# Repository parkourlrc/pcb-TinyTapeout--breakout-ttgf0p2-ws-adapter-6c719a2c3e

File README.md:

# Tiny Tapeout GF 0p2 mezzanine adapter PCB

&emsp;

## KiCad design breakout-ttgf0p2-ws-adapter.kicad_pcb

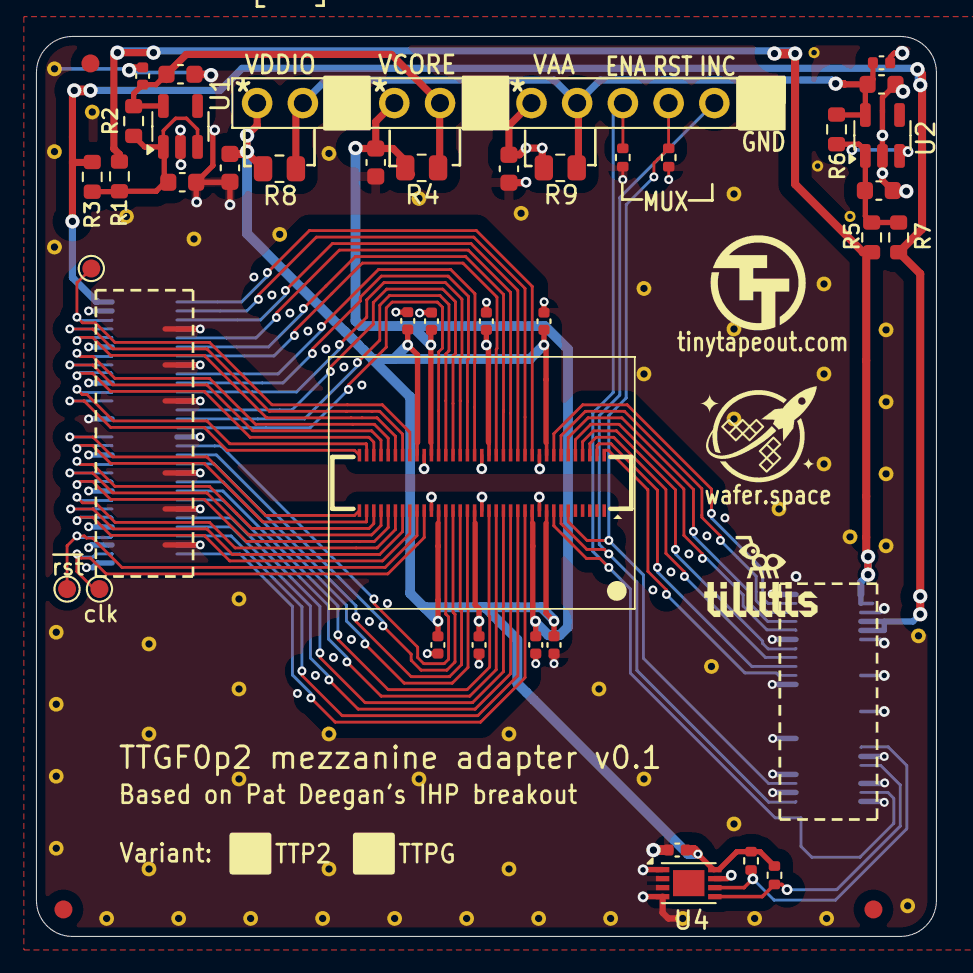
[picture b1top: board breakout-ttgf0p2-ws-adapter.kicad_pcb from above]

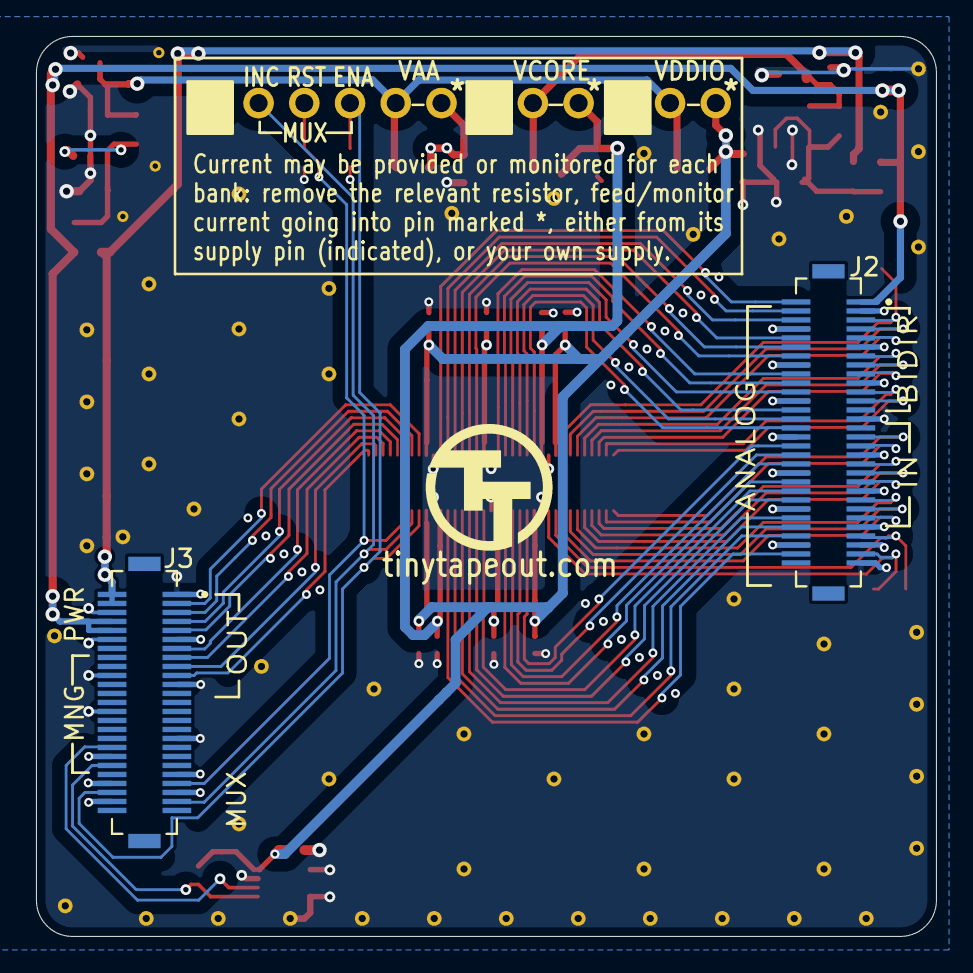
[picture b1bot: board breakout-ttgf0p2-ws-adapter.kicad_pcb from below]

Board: 4 copper layers, 50.0 x 50.0 mm, 107 parts (3 on the bottom side), 63 nets.

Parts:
C1, C2, C4, C5, C6, C8, C9: 10uF; C_0603_1608Metric
C3, C7, C15: 100nF; C_0402_1005Metric
C10, C11, C12, C13, C14, C16, C17, C18: 1u; C_0402_1005Metric
FID1, FID2, FID3: Fiducial; Fiducial_1mm_Mask2mm
J1: Conn_01x12; PinHeader_1x12_P2.54mm_Vertical
J2: DF12NB-60DS-0.5V_51; HRS_DF12NB-60DS-0.5V_51
J3: DF12NB-50DS-0.5V_51; HRS_DF12NB-50DS-0.5V_51
R1, R2, R3, R5, R6, R7: 0; R_0603_1608Metric
R4, R8, R9: 0; R_0805_2012Metric
R10, R11: 1k; R_0402_1005Metric
R12, R13: 2k; R_0402_1005Metric
STITCH01, STITCH02, STITCH03, STITCH04, STITCH05, STITCH06, STITCH07, STITCH08, STITCH09, STITCH10, STITCH11, STITCH12, STITCH13, STITCH14, STITCH15, STITCH16, STITCH17, STITCH18, STITCH19, STITCH20, STITCH21, STITCH22, STITCH23, STITCH24, STITCH25, STITCH26, STITCH27, STITCH28, STITCH29, STITCH30, STITCH31, STITCH32, STITCH33, STITCH34, STITCH35, STITCH36, STITCH38, STITCH39, STITCH40, STITCH41, STITCH42, STITCH43, STITCH44, STITCH45, STITCH46, STITCH47, STITCH48, STITCH49, STITCH50, STITCH51, STITCH52, STITCH53, STITCH54, STITCH55, STITCH56, STITCH57: StitchingVia-0.4mmDrill
STITCHSM01, STITCHSM02, STITCHSM03: StitchingVia-0.3mm
TILL1: Tillitis_logo; tillitis_logo
TP1, TP2, TP3: TestPoint; TestPoint_Pad_D1.0mm
TTLOGO1, TTLOGO1#2: TT_logo
U1, U2: AP2112K-3.3; SOT-23-5
U3: TT_GF_0p2_WS; ws_mezzanine_board
U4: 24LC02; DFN-8-1EP_3x2mm_P0.5mm_EP1.75x1.45mm
WS1: Wafer_space_logo; wafer_space_logo

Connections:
+3V3: J2.1, J3.8, J3.10, R3.1, R7.1
+5V: J3.2, J3.4, R1.1, R5.1
/VCOREIN: C1.1, R1.2, R2.1, R3.2, U1.1 (VIN), U1.3 (EN)
/VDIN: C5.1, R5.2, R6.1, R7.2, U2.1 (VIN), U2.3 (EN)
/an0: J2.2, U3.60 (analog[0])
/an1: J2.4, U3.59 (analog[1])
/an2: J2.6, U3.58 (analog[2])
/an3: J2.10, U3.57 (analog[3])
/an4: J2.12, U3.56 (analog[4])
/an5: J2.14, U3.55 (analog[5])
/an6: J2.18, U3.52 (analog[6])
/an7: J2.20, U3.51 (analog[7])
/an8: J2.22, U3.50 (analog[8])
/an9: J2.26, U3.49 (analog[9])
/an10: J2.28, U3.48 (analog[10])
/an11: J2.30, U3.47 (analog[11])
/an12: J2.34, U3.23 (analog[12])
/an13: J2.36, U3.22 (analog[13])
/an14: J2.38, U3.21 (analog[14])
/an15: J2.42, U3.20 (analog[15])
/an16: J2.44, U3.17 (analog[16])
/an17: J2.46, U3.16 (analog[17])
/an18: J2.50, U3.15 (analog[18])
/an19: J2.52, U3.14 (analog[19])
/an20: J2.54, U3.13 (analog[20])
/an21: J2.58, U3.12 (analog[21])
/enable: J1.4, J3.46, R11.1, U3.8 (ctrl_ena)
/increment: J1.2, J3.47, U3.7 (ctrl_sel_inc)
/mngIO1: J3.40, R12.2, U4.5 (SDA)
/mngIO2: J3.36, R13.2, U4.6 (SCL)
/p_clk: J2.57, TP1.1, U3.26 (u_clk)
/rst_n: J1.3, J3.43, R10.1, U3.6 (ctrl_sel_rst_n)
/uin0: J2.31, U3.35 (ui[0])
/uin1: J2.33, U3.34 (ui[1])
/uin2: J2.37, U3.33 (ui[2])
/uin3: J2.39, U3.32 (ui[3])
/uin4: J2.41, U3.31 (ui[4])
/uin5: J2.45, U3.30 (ui[5])
/uin6: J2.47, U3.29 (ui[6])
/uin7: J2.49, U3.28 (ui[7])
/uio0: J2.5, TP3.1, U3.43 (uio[0])
/uio1: J2.7, U3.42 (uio[1])
/uio2: J2.9, U3.41 (uio[2])
/uio3: J2.13, U3.40 (uio[3])
/uio4: J2.15, U3.39 (uio[4])
/uio5: J2.17, U3.38 (uio[5])
/uio6: J2.21, U3.37 (uio[6])
/uio7: J2.23, U3.36 (uio[7])
/uout0: J3.19, U3.70 (uo[0])
/uout1: J3.17, U3.69 (uo[1])
/uout2: J3.15, U3.68 (uo[2])
/uout3: J3.13, U3.67 (uo[3])
/uout4: J3.9, U3.66 (uo[4])
/uout5: J3.7, U3.65 (uo[5])
/uout6: J3.5, U3.64 (uo[6])
/uout7: J3.3, U3.63 (uo[7])
/~p_rst: J2.53, TP2.1, U3.27 (u_rst_n)
GND: C1.2, C2.2, C3.2, C4.2, C5.2, C6.2, C7.2, C8.2, C9.2, C10.2, C11.2, C12.2, C13.2, C14.2, C15.1, C16.2, C17.2, C18.2, J1.1, J1.7, J1.10, J2.3, J2.8, J2.11, J2.16, J2.19, J2.24, J2.27, J2.32, J2.35, J2.40, J2.43, J2.48, J2.51, J2.55, J2.56, J2.59, J3.1, J3.6, J3.11, J3.12, J3.20, J3.21, J3.28, J3.33, J3.38, J3.41, J3.44, J3.45, J3.48, R10.2, R11.2, STITCH01.1, STITCH02.1, STITCH03.1, STITCH04.1, STITCH05.1, STITCH06.1, STITCH07.1, STITCH08.1, STITCH09.1, STITCH10.1, STITCH11.1, STITCH12.1, STITCH13.1, STITCH14.1, STITCH15.1, STITCH16.1, STITCH17.1, STITCH18.1, STITCH19.1, STITCH20.1, STITCH21.1, STITCH22.1, STITCH23.1, STITCH24.1, STITCH25.1, STITCH26.1, STITCH27.1, STITCH28.1, STITCH29.1, STITCH30.1, STITCH31.1, STITCH32.1, STITCH33.1, STITCH34.1, STITCH35.1, STITCH36.1, STITCH38.1, STITCH39.1, STITCH40.1, STITCH41.1, STITCH42.1, STITCH43.1, STITCH44.1, STITCH45.1, STITCH46.1, STITCH47.1, STITCH48.1, STITCH49.1, STITCH50.1, STITCH51.1, STITCH52.1, STITCH53.1, STITCH54.1, STITCH55.1, STITCH56.1, STITCH57.1, STITCHSM01.1, STITCHSM02.1, STITCHSM03.1, U1.2 (GND), U2.2 (GND), U3.10 (GND), U3.18 (GND), U3.25 (GND), U3.45 (GND), U3.53 (GND), U3.61 (GND), U4.1 (A0), U4.2 (A1), U4.3 (A2), U4.4 (GND), U4.7 (WP)
VAA: C8.1, C16.1, C17.1, J1.6, R9.2, U3.19 (VAA_Analog), U3.54 (VAA_Analog)
VCORE_{REG}: C2.1, C3.1, J1.8, R2.2, R4.1, U1.5 (VOUT)
VDD_{CORE}: C4.1, C13.1, C14.1, J1.9, R4.2, U3.11 (VDD_Core), U3.46 (VDD_Core)
VDD_{IO}: C9.1, C10.1, C11.1, C12.1, C15.2, C18.1, J1.12, R8.2, R12.1, R13.1, U3.9 (VDD_IO), U3.24 (VDD_IO), U3.44 (VDD_IO), U3.62 (VDD_IO), U4.8 (VCC)
VIO_{REG}: C6.1, C7.1, J1.5, J1.11, R6.2, R8.1, R9.1, U2.5 (VOUT)

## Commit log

2026-03-23 initial version
